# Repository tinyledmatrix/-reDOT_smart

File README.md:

# -reDOT_smart
Files for my  reDOT_smart project

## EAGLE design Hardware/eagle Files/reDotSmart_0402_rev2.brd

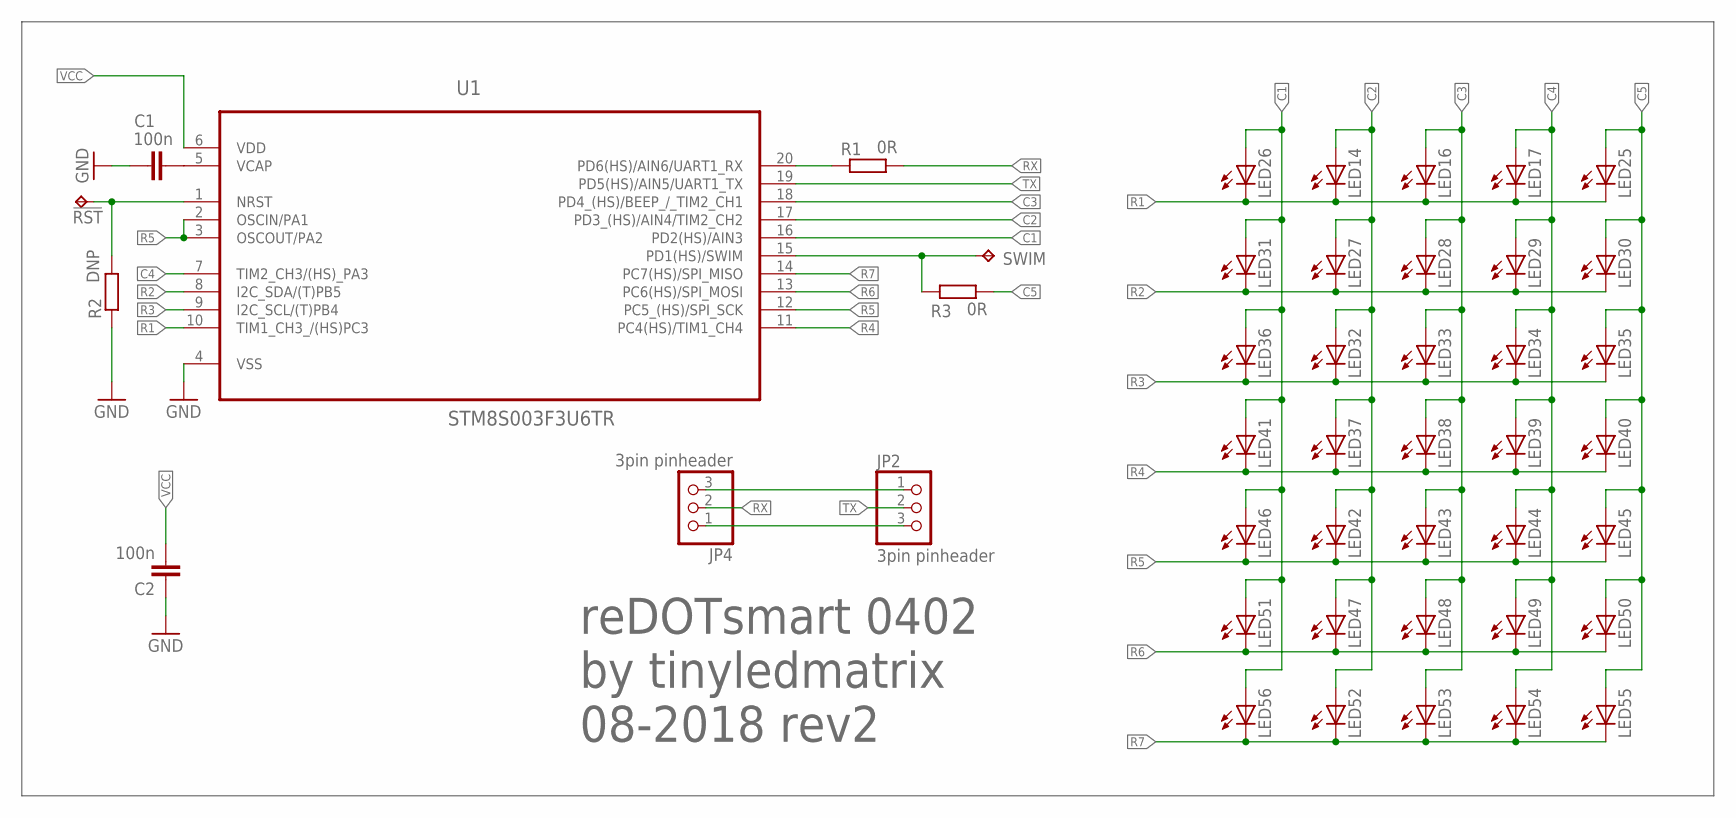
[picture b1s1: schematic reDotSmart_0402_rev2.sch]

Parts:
!RST: TPTP10R; TP10R
C1, C2: 100n; C0402-VISHAY
JP2, JP4: 3pin pinheader; 1X03_ROUND_NOSM
LED14, LED16, LED17, LED25, LED26, LED27, LED28, LED29, LED30, LED31, LED32, LED33, LED34, LED35, LED36, LED37, LED38, LED39, LED40, LED41, LED42, LED43, LED44, LED45, LED46, LED47, LED48, LED49, LED50, LED51, LED52, LED53, LED54, LED55, LED56: LED0402_ROHM; LED0402_E_ROHM_SML-P1
R1: 0R; ADAFRUIT_R0402-VISHAY
R2: DNP; ADAFRUIT_R0402-VISHAY
R3: 0R; ADAFRUIT_R0603-VISHAY
SWIM: TPTP10R; TP10R
U1: STM8S003F3U6TR; QFN50P300X300X100-20N_STM

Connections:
C1: LED26.A, LED31.A, LED36.A, LED41.A, LED46.A, LED51.A, LED56.A, U1.16 (PD2(HS)/AIN3)
C2: LED14.A, LED27.A, LED32.A, LED37.A, LED42.A, LED47.A, LED52.A, U1.17 (PD3_(HS)/AIN4/TIM2_CH2)
C3: LED16.A, LED28.A, LED33.A, LED38.A, LED43.A, LED48.A, LED53.A, U1.18 (PD4_(HS)/BEEP_/_TIM2_CH1)
C4: LED17.A, LED29.A, LED34.A, LED39.A, LED44.A, LED49.A, LED54.A, U1.7 (TIM2_CH3/(HS)_PA3)
C5: LED25.A, LED30.A, LED35.A, LED40.A, LED45.A, LED50.A, LED55.A, R3.2
GND: C1.1, C2.1, JP2.1, JP4.3, R2.1, U1.4 (VSS)
unnamed: R1.1, U1.20 (PD6(HS)/AIN6/UART1_RX)
unnamed: R3.1, SWIM.TP, U1.15 (PD1(HS)/SWIM)
unnamed: C1.2, U1.5 (VCAP)
NRST: !RST.TP, R2.2, U1.1 (NRST)
R1: LED14.K (C), LED16.K (C), LED17.K (C), LED25.K (C), LED26.K (C), U1.10 (TIM1_CH3_/(HS)PC3)
R2: LED27.K (C), LED28.K (C), LED29.K (C), LED30.K (C), LED31.K (C), U1.8 (I2C_SDA/(T)PB5)
R3: LED32.K (C), LED33.K (C), LED34.K (C), LED35.K (C), LED36.K (C), U1.9 (I2C_SCL/(T)PB4)
R4: LED37.K (C), LED38.K (C), LED39.K (C), LED40.K (C), LED41.K (C), U1.11 (PC4(HS)/TIM1_CH4)
R5: LED42.K (C), LED43.K (C), LED44.K (C), LED45.K (C), LED46.K (C), U1.2 (OSCIN/PA1), U1.3 (OSCOUT/PA2), U1.12 (PC5_(HS)/SPI_SCK)
R6: LED47.K (C), LED48.K (C), LED49.K (C), LED50.K (C), LED51.K (C), U1.13 (PC6(HS)/SPI_MOSI)
R7: LED52.K (C), LED53.K (C), LED54.K (C), LED55.K (C), LED56.K (C), U1.14 (PC7(HS)/SPI_MISO)
RX: JP4.2, R1.2
TX: JP2.2, U1.19 (PD5(HS)/AIN5/UART1_TX)
VCC: C2.2, JP2.3, JP4.1, U1.6 (VDD)

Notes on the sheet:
reDOTsmart 0402 by tinyledmatrix 08-2018 rev2

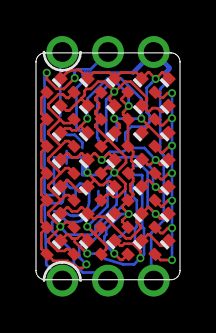
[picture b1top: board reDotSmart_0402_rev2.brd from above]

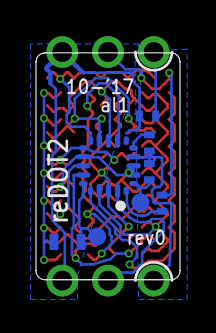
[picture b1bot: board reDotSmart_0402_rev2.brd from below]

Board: 2 copper layers, 8.0 x 12.6 mm, 45 parts (8 on the bottom side), 20 nets.

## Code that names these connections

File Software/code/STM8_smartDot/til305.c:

/* 
small code to controll one TIL305 with STM8S103F3

Pinmapping:

 COL:	2/	1/	3/	4/	5/
	PD3	PD2	PD4	PA3	PD1
ROW:
1 / PB4	X	X	X	X	X
2 / PB5	X	X	X	X	X
3 / PC3 X	X	X	X	X
4 / PC4	X	X	X	X	X
5 / PC5	X	X	X	X	X
6 / PC6	X	X	X	X	X
7 / PC7	X	X	X	X	X
	
*/


#include "til305.h"
#include "font5x7.h"

#define COLS_PORTD_MASK 0x1E 	// mask for cols on port D D1:D4
#define COLS_PORTA_MASK 0x08	// mask for cols on port A A3
#define ROWS_PORTB_MASK 0x30	// mask for rows on port B B4:B5
#define ROWS_PORTC_MASK 0xF8	// mask for rows on port C C3:C7

const unsigned char colBitMask[5] = {(1<<2), (1<<3), (1<<4), (1<<3), (1<<1)};

volatile unsigned char colCounter;//=0;
volatile unsigned char displayBuffer[5];//={0, 0xff, 0xff,0,0} ;

char myChar='H';

void reDot_displayASCII(char index)
{
	index-=32;
	if (index>95) // if ascii>127
        	return;
     	displayBuffer[0]=Font5x7[index][0];
     	displayBuffer[1]=Font5x7[index][1];
     	displayBuffer[2]=Font5x7[index][2];
     	displayBuffer[3]=Font5x7[index][3];
     	displayBuffer[4]=Font5x7[index][4];  
}  

// Timer1 Update/Overflow/Trigger/Break Interrupt
INTERRUPT_HANDLER(TIM1_UPD_OVF_TRG_BRK_IRQHandler, 11){
	if(TIM1_SR1 & TIM_SR1_UIF)
	{ 
		colCounter++;
		if (colCounter>4) colCounter=0;
		
		PB_ODR |= ROWS_PORTB_MASK;    // set all rows to high = off 
		PC_ODR |= ROWS_PORTC_MASK;

		PD_ODR &= ~COLS_PORTD_MASK;	// cols off
		//PA_ODR &= ~COLS_PORTA_MASK;
		PA_ODR = 0;

		//PB_ODR &= ~( (displayBuffer[colCounter] & 0x03)<<4);
		//PC_ODR &= ~( (displayBuffer[colCounter] & 0x7C)<<1); 
		PB_ODR = ~( (displayBuffer[colCounter] )<<4);
		PC_ODR = ~( (displayBuffer[colCounter] )<<1);
		

		if (colCounter==3)
		{	
			PA_ODR |= colBitMask[colCounter];
		}
		else
		{
			PD_ODR |= colBitMask[colCounter];
		}
	}
	TIM1_SR1 = 0; // clear all interrupt flags
}


void reDot_init (void)
{
	PD_DDR = COLS_PORTD_MASK;	//set all cols to push-pull output 
	PA_DDR = COLS_PORTA_MASK;
	PD_CR1 = COLS_PORTD_MASK;
	PA_CR1 = COLS_PORTA_MASK;

	PB_DDR = ROWS_PORTB_MASK;    	// set all row to (true) open drain outputs 
	PC_DDR = ROWS_PORTC_MASK;
	PB_ODR = ROWS_PORTB_MASK;    	// set all rows to high = off 
	PC_ODR = ROWS_PORTC_MASK;

	TIM1_ARRH = 0x01;
	TIM1_ARRL = 0xD0;

	TIM1_IER = TIM_IER_UIE; 	// interrupts: update
	TIM1_CR1 = TIM_CR1_APRE | TIM_CR1_URS | TIM_CR1_CEN; // auto-reload + interrupt on overflow + enable

}

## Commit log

2018-08-31 First push Hardware
    eagle Files
    Gerbers
    PCB, SCH as png
    BOM as csv
2018-09-30 First fimwre Versions
    Added early firmwre version
